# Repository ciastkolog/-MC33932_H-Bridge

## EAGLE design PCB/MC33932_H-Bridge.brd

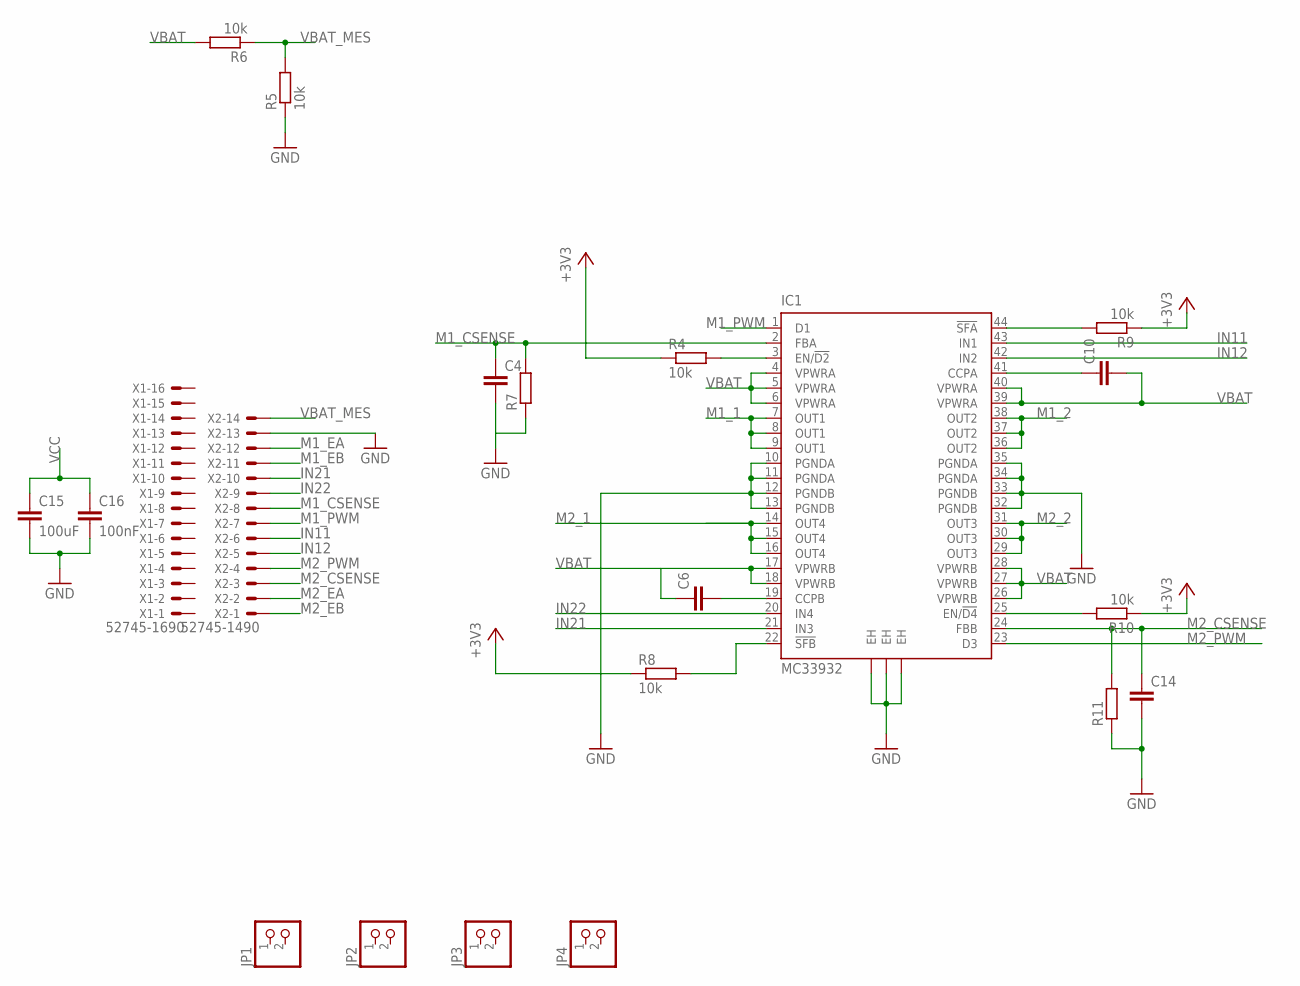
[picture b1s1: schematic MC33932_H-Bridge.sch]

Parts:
C4, C14: C-EUC0603; C0603
C6, C10: C-EUC0805; C0805
C15: 100uF; C1210K
C16: 100nF; C0603
IC1: MC33932; HSOP44
JP1, JP2, JP3, JP4: PINHD-1X2; 1X02
R4, R5, R6, R8, R9, R10: 10k; R0603
R7, R11: R-EU_R0603; R0603
X1: 52745-1690
X2: 52745-1490

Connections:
+3V3: R4.1, R8.1, R9.1, R10.1
GND: C4.2, C14.2, C15.2, C16.2, IC1.10 (PGNDA), IC1.11 (PGNDA), IC1.12 (PGNDB), IC1.13 (PGNDB), IC1.32 (PGNDB), IC1.33 (PGNDB), IC1.34 (PGNDA), IC1.35 (PGNDA), IC1.EH@1 (EH), IC1.EH@2 (EH), IC1.EH@3 (EH), R5.1, R7.1, R11.1, X2.13
IN11: IC1.43 (IN1), X2.6
IN12: IC1.42 (IN2), X2.5
IN21: IC1.21 (IN3), X2.10
IN22: IC1.20 (IN4), X2.9
M1_1: IC1.7 (OUT1), IC1.8 (OUT1), IC1.9 (OUT1)
M1_2: IC1.36 (OUT2), IC1.37 (OUT2), IC1.38 (OUT2)
M1_CSENSE: C4.1, IC1.2 (FBA), R7.2, X2.8
M1_EA: X2.12
M1_EB: X2.11
M1_PWM: IC1.1 (D1), X2.7
M2_1: IC1.14 (OUT4), IC1.15 (OUT4), IC1.16 (OUT4)
M2_2: IC1.29 (OUT3), IC1.30 (OUT3), IC1.31 (OUT3)
M2_CSENSE: C14.1, IC1.24 (FBB), R11.2, X2.3
M2_EA: X2.2
M2_EB: X2.1
M2_PWM: IC1.23 (D3), X2.4
unnamed: C10.1, IC1.41 (CCPA)
unnamed: IC1.3 (EN/!D2), R4.2
unnamed: C6.2, IC1.19 (CCPB)
unnamed: IC1.22 (!SFB), R8.2
unnamed: IC1.25 (EN/!D4), R10.2
unnamed: IC1.44 (!SFA), R9.2
VBAT: C6.1, C10.2, IC1.4 (VPWRA), IC1.5 (VPWRA), IC1.6 (VPWRA), IC1.17 (VPWRB), IC1.18 (VPWRB), IC1.26 (VPWRB), IC1.27 (VPWRB), IC1.28 (VPWRB), IC1.39 (VPWRA), IC1.40 (VPWRA), R6.2
VBAT_MES: R5.2, R6.1, X2.14
VCC: C15.1, C16.1

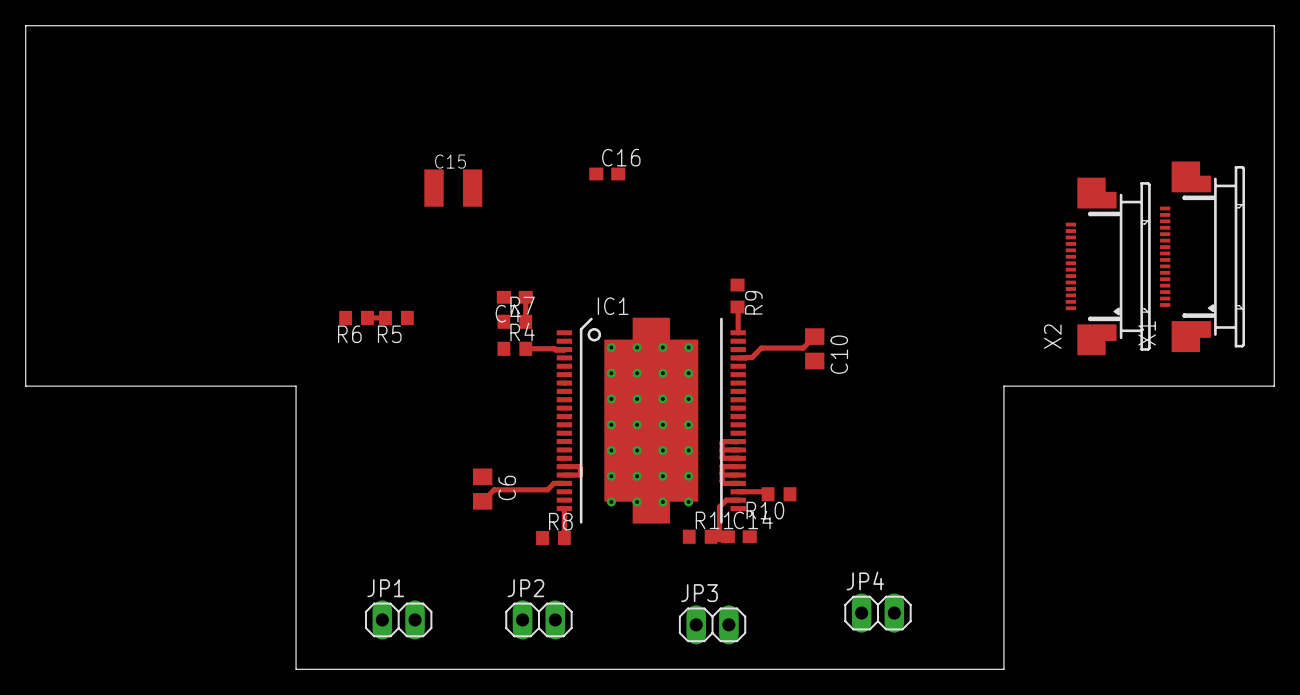
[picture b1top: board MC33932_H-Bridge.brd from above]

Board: 2 copper layers, 97.0 x 50.0 mm, 21 parts (0 on the bottom side), 23 nets.

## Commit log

2018-03-06 Add documentation
2018-03-06 Add schema
